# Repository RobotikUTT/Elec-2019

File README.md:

# Elec-2019
Kicad PCB and libraries designed

# Elec-2021
- CAN on sonar not working, needs to be redone. 
- Rebuy MCP2515-18Lead and MCP2551-I/P (CAN components)
- Recheck PCB routing (maybe redo some)

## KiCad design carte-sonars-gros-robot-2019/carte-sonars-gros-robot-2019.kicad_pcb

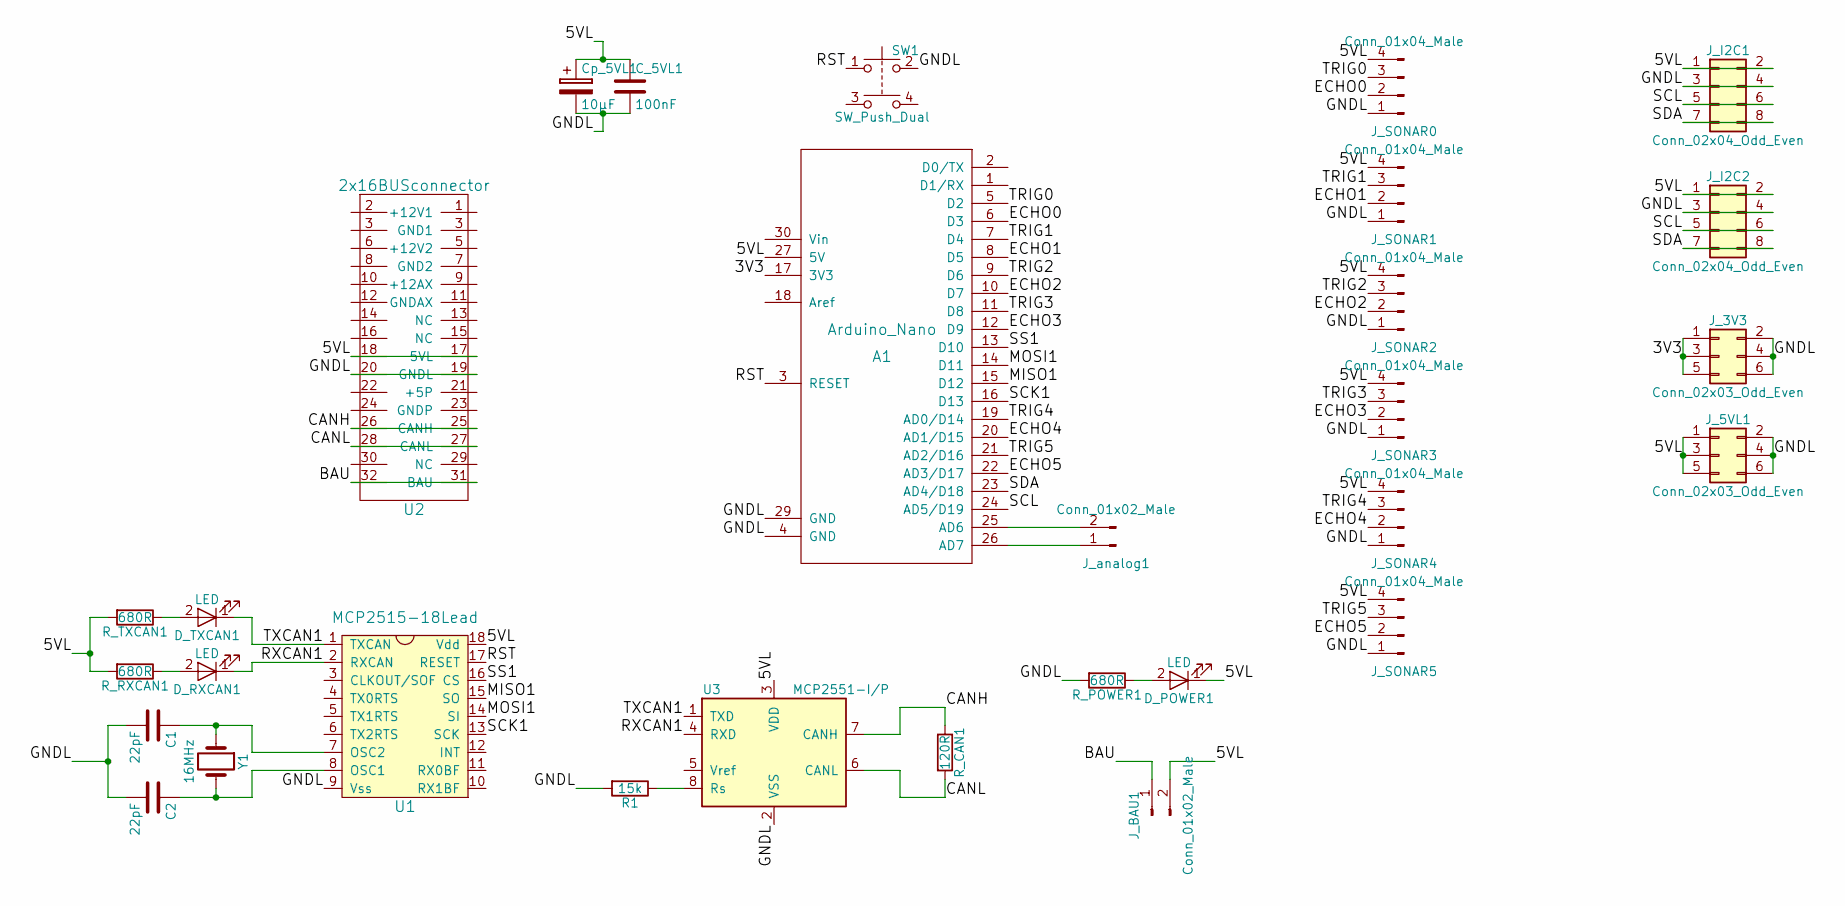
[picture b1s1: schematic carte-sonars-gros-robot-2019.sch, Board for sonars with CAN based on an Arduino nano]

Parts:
A1: Arduino_Nano; arduino_nano
C1, C2: 22pF; C_Disc_D3.4mm_W2.1mm_P2.50mm
C_5VL1: 100nF; C_Disc_D3.4mm_W2.1mm_P2.50mm
Cp_5VL1: 10µF; CP_Radial_D5.0mm_P2.50mm
D_POWER1: LED; LED_D3.0mm
D_RXCAN1: LED; LED_D3.0mm
D_TXCAN1: LED; LED_D3.0mm
J_3V3, J_5VL1: Conn_02x03_Odd_Even; Pin_Header_Straight_2x03_Pitch2.54mm
J_BAU1: Conn_01x02_Male; Pin_Header_Straight_1x02_Pitch2.54mm
J_I2C1, J_I2C2: Conn_02x04_Odd_Even; Pin_Header_Straight_2x04_Pitch2.54mm
J_SONAR0, J_SONAR1, J_SONAR2, J_SONAR3, J_SONAR4, J_SONAR5: Conn_01x04_Male; Pin_Header_Straight_1x04_Pitch2.54mm
J_analog1: Conn_01x02_Male; Pin_Header_Straight_1x02_Pitch2.54mm
R1: 15k; R_Axial_DIN0207_L6.3mm_D2.5mm_P7.62mm_Horizontal
R_CAN1: 120R; R_Axial_DIN0207_L6.3mm_D2.5mm_P7.62mm_Horizontal
R_POWER1: 680R; R_Axial_DIN0207_L6.3mm_D2.5mm_P7.62mm_Horizontal
R_RXCAN1: 680R; R_Axial_DIN0207_L6.3mm_D2.5mm_P7.62mm_Horizontal
R_TXCAN1: 680R; R_Axial_DIN0207_L6.3mm_D2.5mm_P7.62mm_Horizontal
SW1: SW_Push_Dual; SW_TH_Tactile_Omron_B3F-10xx
U1: MCP2515-18Lead; DIP-18_W7.62mm_Socket_LongPads
U2: 2x16BUSconnector; Pin_Header_Angled_2x16_Pitch2.54mm
U3: MCP2551-I/P; DIP-8_W7.62mm
Y1: 16MHz; Crystal_SMD_HC49-SD_HandSoldering

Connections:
/3V3: A1.17 (3V3), J_3V3.1, J_3V3.3, J_3V3.5
/5VL: A1.27 (5V), C_5VL1.1, Cp_5VL1.1, D_POWER1.1 (K), J_5VL1.1, J_5VL1.3, J_5VL1.5, J_BAU1.2, J_I2C1.1, J_I2C1.2, J_I2C2.1, J_I2C2.2, J_SONAR0.4, J_SONAR1.4, J_SONAR2.4, J_SONAR3.4, J_SONAR4.4, J_SONAR5.4, R_RXCAN1.2, R_TXCAN1.2, U1.18 (Vdd), U2.17 (5VL), U2.18, U3.3 (VDD)
/BAU: J_BAU1.1, U2.31 (BAU), U2.32
/CANH: R_CAN1.1, U2.25 (CANH), U2.26, U3.7 (CANH)
/CANL: R_CAN1.2, U2.27 (CANL), U2.28, U3.6 (CANL)
/ECHO0: A1.6 (D3), J_SONAR0.2
/ECHO1: A1.8 (D5), J_SONAR1.2
/ECHO2: A1.10 (D7), J_SONAR2.2
/ECHO3: A1.12 (D9), J_SONAR3.2
/ECHO4: A1.20 (AD1/D15), J_SONAR4.2
/ECHO5: A1.22 (AD3/D17), J_SONAR5.2
/GNDL: A1.4 (GND), A1.29 (GND), C1.2, C2.2, C_5VL1.2, Cp_5VL1.2, J_3V3.2, J_3V3.4, J_3V3.6, J_5VL1.2, J_5VL1.4, J_5VL1.6, J_I2C1.3, J_I2C1.4, J_I2C2.3, J_I2C2.4, J_SONAR0.1, J_SONAR1.1, J_SONAR2.1, J_SONAR3.1, J_SONAR4.1, J_SONAR5.1, R1.2, R_POWER1.2, SW1.2, U1.9 (Vss), U2.19 (GNDL), U2.20, U3.2 (VSS)
/MISO1: A1.15 (D12), U1.15 (SO)
/MOSI1: A1.14 (D11), U1.14 (SI)
/RST: A1.3 (RESET), SW1.1, U1.17 (RESET)
/RXCAN1: D_RXCAN1.1 (K), U1.2 (RXCAN), U3.4 (RXD)
/SCK1: A1.16 (D13), U1.13 (SCK)
/SCL: A1.24 (AD5/D19), J_I2C1.5, J_I2C1.6, J_I2C2.5, J_I2C2.6
/SDA: A1.23 (AD4/D18), J_I2C1.7, J_I2C1.8, J_I2C2.7, J_I2C2.8
/SS1: A1.13 (D10), U1.16 (CS)
/TRIG0: A1.5 (D2), J_SONAR0.3
/TRIG1: A1.7 (D4), J_SONAR1.3
/TRIG2: A1.9 (D6), J_SONAR2.3
/TRIG3: A1.11 (D8), J_SONAR3.3
/TRIG4: A1.19 (AD0/D14), J_SONAR4.3
/TRIG5: A1.21 (AD2/D16), J_SONAR5.3
/TXCAN1: D_TXCAN1.1 (K), U1.1 (TXCAN), U3.1 (TXD)
unnamed: A1.25 (AD6), J_analog1.2
unnamed: A1.26 (AD7), J_analog1.1
unnamed: C1.1, U1.7 (OSC2), Y1.1
unnamed: C2.1, U1.8 (OSC1), Y1.2
unnamed: D_POWER1.2 (A), R_POWER1.1
unnamed: D_RXCAN1.2 (A), R_RXCAN1.1
unnamed: D_TXCAN1.2 (A), R_TXCAN1.1
unnamed: R1.1, U3.8 (Rs)

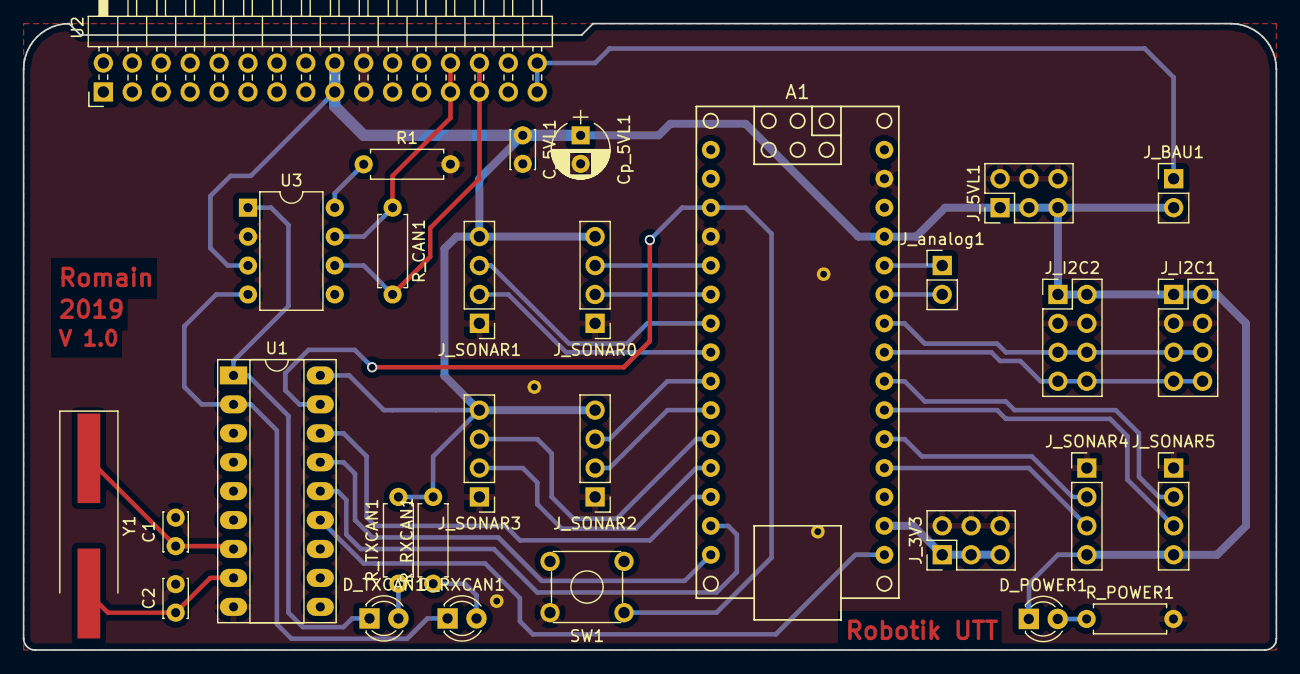
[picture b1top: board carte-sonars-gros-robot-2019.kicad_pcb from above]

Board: 2 copper layers, 110.0 x 55.0 mm, 30 parts (0 on the bottom side), 35 nets.

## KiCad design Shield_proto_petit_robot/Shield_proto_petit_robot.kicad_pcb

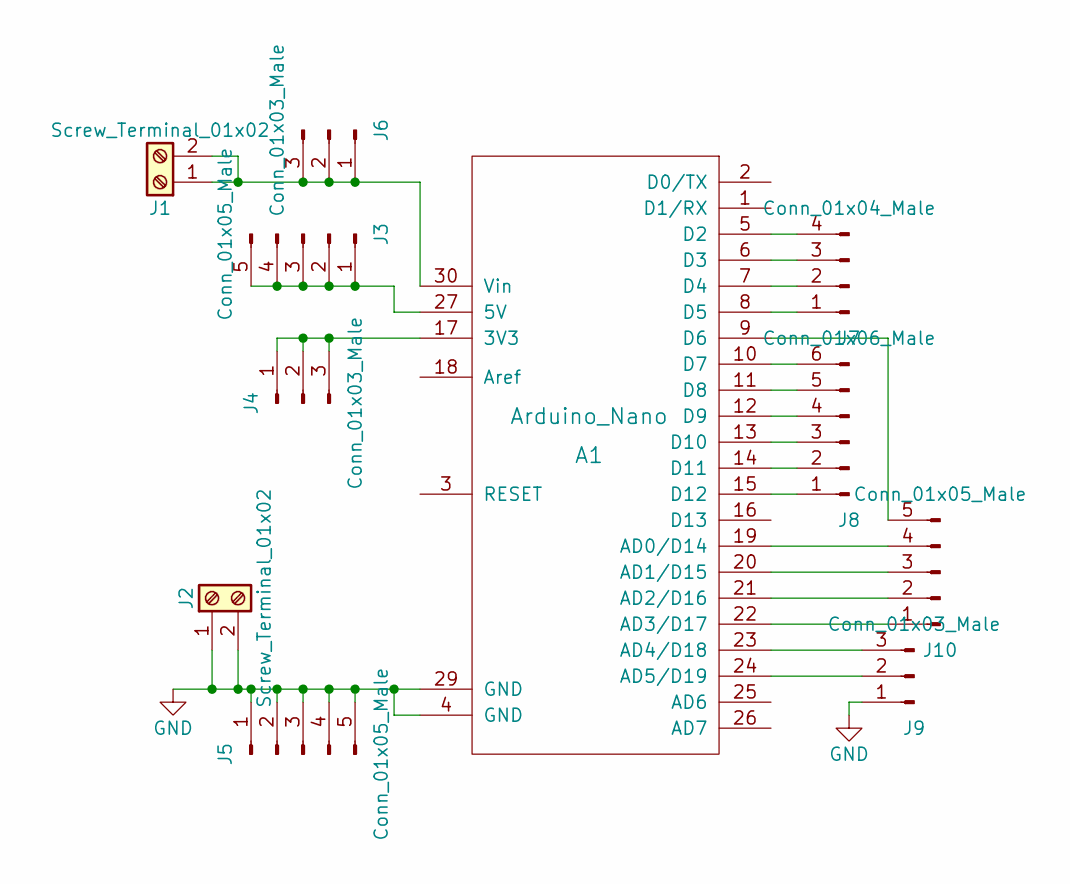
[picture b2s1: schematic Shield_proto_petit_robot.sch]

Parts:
A1: Arduino_Nano; arduino_nano
J1, J2: Screw_Terminal_01x02; TerminalBlock_Pheonix_MPT-2.54mm_2pol
J3, J5, J10: Conn_01x05_Male; Pin_Header_Straight_1x05_Pitch2.54mm
J4, J6, J9: Conn_01x03_Male; Pin_Header_Straight_1x03_Pitch2.54mm
J7: Conn_01x04_Male; Pin_Header_Straight_1x04_Pitch2.54mm
J8: Conn_01x06_Male; Pin_Header_Straight_1x06_Pitch2.54mm

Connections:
GND: A1.4 (GND), A1.29 (GND), J2.1, J2.2, J5.1, J5.2, J5.3, J5.4, J5.5, J9.1
unnamed: A1.5 (D2), J7.4
unnamed: A1.6 (D3), J7.3
unnamed: A1.7 (D4), J7.2
unnamed: A1.8 (D5), J7.1
unnamed: A1.9 (D6), J10.5
unnamed: A1.10 (D7), J8.6
unnamed: A1.11 (D8), J8.5
unnamed: A1.12 (D9), J8.4
unnamed: A1.13 (D10), J8.3
unnamed: A1.14 (D11), J8.2
unnamed: A1.15 (D12), J8.1
unnamed: A1.17 (3V3), J4.1, J4.2, J4.3
unnamed: A1.19 (AD0/D14), J10.4
unnamed: A1.20 (AD1/D15), J10.3
unnamed: A1.21 (AD2/D16), J10.2
unnamed: A1.22 (AD3/D17), J10.1
unnamed: A1.23 (AD4/D18), J9.3
unnamed: A1.24 (AD5/D19), J9.2
unnamed: A1.27 (5V), J3.1, J3.2, J3.3, J3.4, J3.5
unnamed: A1.30 (Vin), J1.1, J1.2, J6.1, J6.2, J6.3

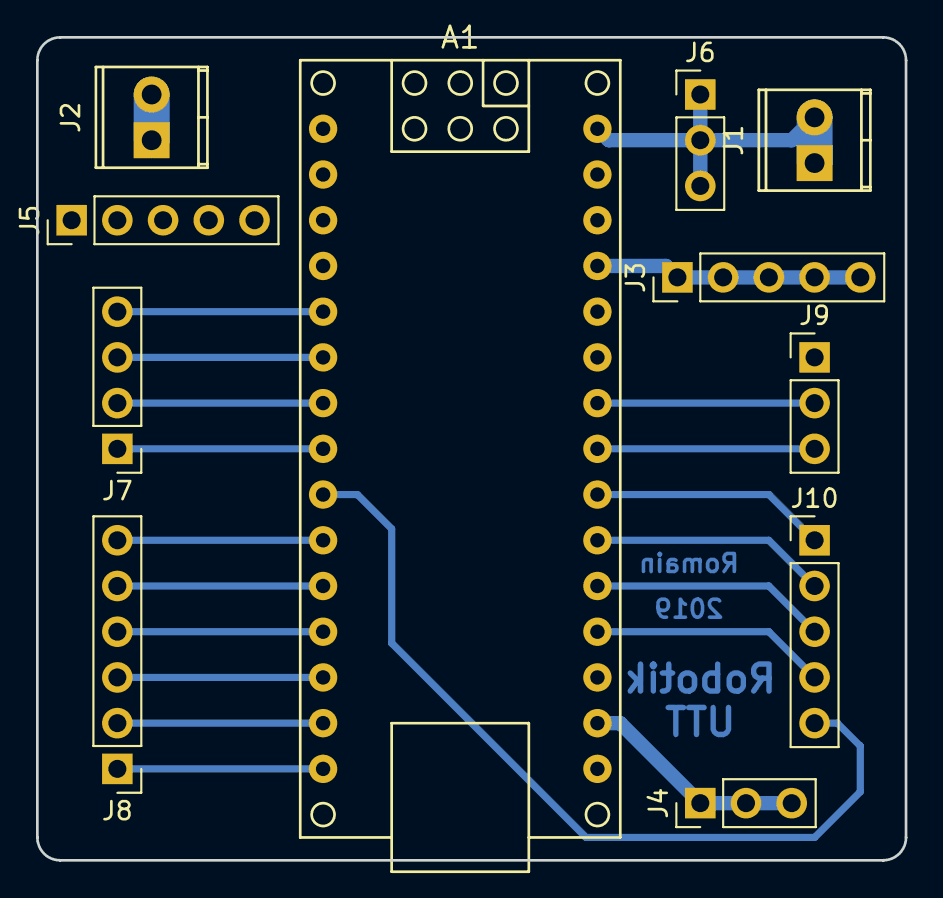
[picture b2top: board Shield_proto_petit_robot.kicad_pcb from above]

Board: 2 copper layers, 48.3 x 45.7 mm, 11 parts (0 on the bottom side), 21 nets.

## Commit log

2019-05-25 adding first files with PCBs
2019-05-25 ending schematic and generating .net file for carte sonars PCB
2019-05-26 PCB routing almost finished
2019-06-30 PCB completed
2021-01-31 2021 Robot
